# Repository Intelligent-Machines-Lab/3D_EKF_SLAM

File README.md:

# 3D EKF SLAM

<div align="center">
	<table>
	  <tr>
	    <td>Experiment</td>
	     <td>High Level reconstruction</td>
	     <td>Point cloud reconstruction</td>
	  </tr>
	  <tr>
	    <td></td>
	    <td></td>
	    <td></td>
	  </tr>
	 </table>
</div>

This repository contains the work from [Leonardo Mariga](https://github.com/leomariga) .

### [Thesis PDF](https://github.com/Intelligent-Machines-Lab/3D_EKF_SLAM/blob/main/Publications/Leonardo_Mariga_MSc_Dissertation_ITA_2021.pdf) | [Videos](https://github.com/Intelligent-Machines-Lab/3D_EKF_SLAM/tree/main/Videos) | [Presentation](https://github.com/Intelligent-Machines-Lab/3D_EKF_SLAM/blob/main/Publications/Presentation/Leonardo%20Mariga%20Master%20presentation.pdf)

> **Solving the Simultaneous Localization and 3D Mapping Problem in Mobile Robotics Using Multi-Level Parameterized Representations**<br>
> Author: **Leonardo Mariga (ITA)**
> Advisor: Prof. Dr. Cairo Lúcio Nascimento Júnior (ITA)
>
> **Simplified Abstract:** *This work proposes an expansion of the traditional landmark-based EKF-SLAM for 3D indoor environments. It uses a mobile robot with an RGBD camera to decompose a scene and update its 3dof location. A point-cloud map is reconstructed by initially simplifying the scene into cylinders and planes. Then, its points are segmented and associated to their specific EKF feature. This enables to output a map using different levels of abstraction, which is helpful when working in applications with limited memory requirements. In our feature extraction method, the RANSAC is used for planar segmentation. The non-planar points are clustered using DB-SCAN and parameterized as cylinders after passing through validation gates. On each step, the classical EKF framework propagates and updates the features' states. This also triggers the point-cloud growth and increments the point-cloud of the observed feature. Our simulation results shows that this method successfully reconstructs maps, reducing the IAE criteria to 15% of trajectory error compared to the odometry. Finally, we sucessfully validate the real environment, using a Intel RealSense camera.*

## 3D EKF SLAM: how does it work?

An overview the algorithm is illustrated in figure below as a V-shaped process. The vertical axis represents map density (which is related to its level of abstraction) and the horizontal axis is the processing order. Starting as a point cloud input and going down to a simplified primitive and parameterized local scene, the features are associated and merged to a global map.

By doing that, the robot's pose is corrected and a global high level map can be generated using the parameterized feature. If the application chooses to carry the point cloud, it can create a point cloud or voxel-based maps as output.

<div align="center">
  <br>
</div>

## Results:

### Simulation results

Simulation results shows that in spite of the odometry error slowly increasing and reaching 7 m, the estimated trajectory error is always within bounds of 1 m. As a quantification tool, we can use the  Integral Absolute Error (IAE) criteria to measure the overall error during the whole SLAM process. Table shows the IAE criteria for this case.The odometry path error is the error related to the concatenation of commands sent to the robot and the estimated path error is obtained from comparing the proposed algorithm with the real path. 

<div align="center">
	<table>
	  <tr>
	    <td></td>
	     <td>IAE Criteria</td>
	  </tr>
	  <tr>
	    <td>Odometry path error</td>
	    <td>304.28</td>
	  </tr>
	  <tr>
	    <td>Our estimation error</td>
	    <td>49.82</td>
	  </tr>
	 </table>
</div>

<div align="center">
  <br>
</div>

### Experimental results

Below are some samples of reconstructed environment with a Intel RealSense RGBD camera. 

<div align="center">
	<table>
	  <tr>
	    <td>Experiment</td>
	     <td>High Level reconstruction</td>
	     <td>Point cloud reconstruction</td>
	  </tr>
	  <tr>
	    <td></td>
	    <td></td>
	    <td></td>
	  </tr>
	  <tr>
	    <td></td>
	    <td></td>
	    <td></td>
	  </tr>
	 </table>
</div>

## Why use this method?

This algorithm uses a cylinder-and-plane combination to reconstruct a parameterized environment, and at the same time, correct the robot's pose. Different from point cloud registration techniques, the proposed algorithm does not match consecutive frames on each other. Actually, it interprets the scene and classifies each point cloud to an EKF feature. **Consequently, our solution is not only a basic SLAM technique but also a strategy for scene understanding and object segmentation.** 

Though the point cloud can be used to reconstruct a colored realistic environment, the algorithm only requires the parameterized environment to work. Therefore, it can operate in machines with different memory configurations 

### Main contributions

The main contributions of this work can be summarize as follows:

 - Use multiple abstraction layers to build a point cloud map on a landmark-based EKF-SLAM.
 - Feature growth method for different views of observed planar or arbitrary objects. 
 - Construction of a parameterized hybrid map based of simplification of the point cloud representation.

## Cite this work

```
@mastersthesis{leomariga,
author = {Mariga, Leonardo},
year = {2021},
month = {12},
pages = {123},
school = {Instituto tecnológico de aeronáutica},
title = {Solving the simultaneous localization and 3D mapping problem in mobile robotics using multi-level parameterized representations},
doi = {10.13140/RG.2.2.33836.33926}
}
```

## Contact

Author: [Leonardo Mariga](https://github.com/leomariga) 

E-mail: leomariga@gmail.com

Feel free to contact me.

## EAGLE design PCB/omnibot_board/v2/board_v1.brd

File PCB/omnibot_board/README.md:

# Omni board
The OMNI board manages power supply to the camera mount and allows communication between Arduino Nano and the camera rotation motor.

-----------------

## Schematic
<!-- 
Click [here](https://github.com/Intelligent-Machines-Lab/Omni_3D/blob/master/PCB/omnibot_board/board_v1.pdf) to open the schematic pdf.  -->

<div align="center">
  <b>
</div>

## PCB

<div align="center">
  <b>
</div>

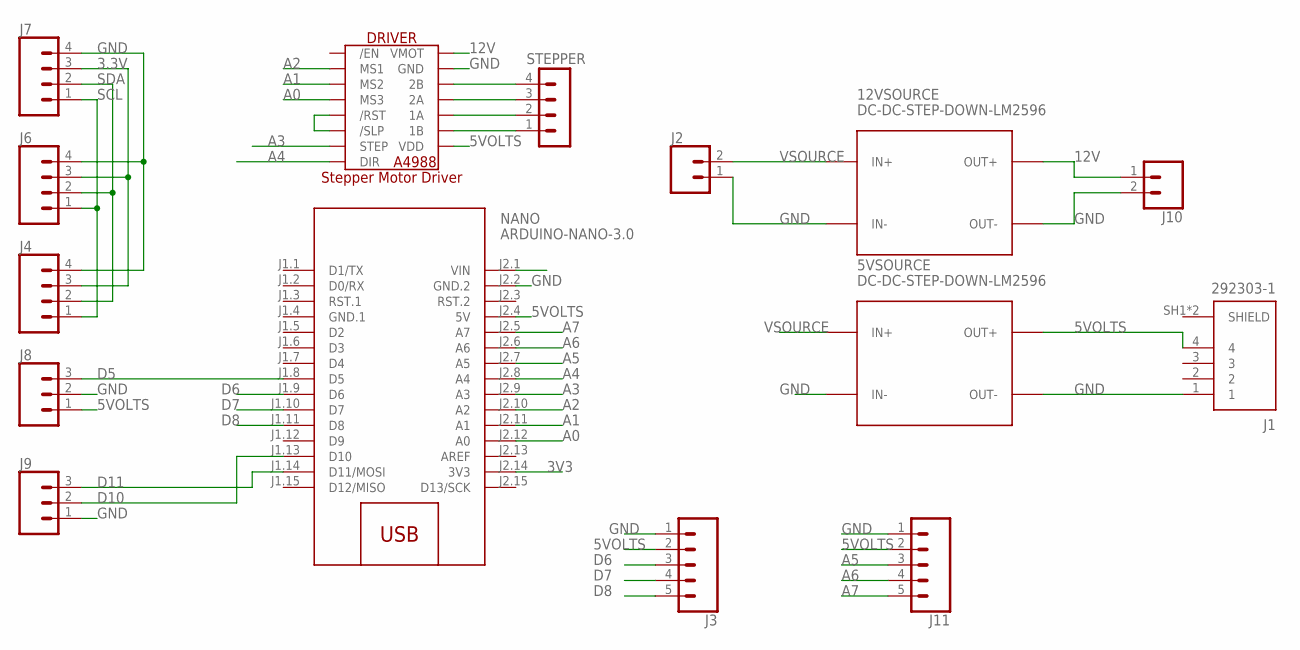
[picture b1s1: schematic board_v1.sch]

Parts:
5VSOURCE, 12VSOURCE: DC-DC-STEP-DOWN-LM2596
DRIVER: A4988_STEP
J1: 292303-1
J2, J10: CONN_025MM; SCREWTERMINAL-5MM-2
J3, J11: CONN_05; 1X05
J4, J6, J7: CONN_04POLAR; MOLEX-1X4
J8, J9: CONN_03POLAR; MOLEX-1X3
NANO: ARDUINO-NANO-3.0
STEPPER: MA04-1

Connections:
3.3V: J4.3, J6.3, J7.3
3V3: NANO.J2.14 (3V3)
5VOLTS: 5VSOURCE.OUT+, DRIVER.VDD, J1.4, J3.2, J8.1, J11.2, NANO.J2.4 (5V)
12V: 12VSOURCE.OUT+, DRIVER.VMOT, J10.1
A0: DRIVER.MS3, NANO.J2.12 (A0)
A1: DRIVER.MS2, NANO.J2.11 (A1)
A2: DRIVER.MS1, NANO.J2.10 (A2)
A3: DRIVER.STEP, NANO.J2.9 (A3)
A4: DRIVER.DIR, NANO.J2.8 (A4)
A5: J11.3, NANO.J2.7 (A5)
A6: J11.4, NANO.J2.6 (A6)
A7: J11.5, NANO.J2.5 (A7)
D5: J8.3, NANO.J1.8 (D5)
D6: J3.3, NANO.J1.9 (D6)
D7: J3.4, NANO.J1.10 (D7)
D8: J3.5, NANO.J1.11 (D8)
D10: J9.2, NANO.J1.13 (D10)
D11: J9.3, NANO.J1.14 (D11/MOSI)
GND: 5VSOURCE.IN-, 5VSOURCE.OUT-, 12VSOURCE.IN-, 12VSOURCE.OUT-, DRIVER.GND, DRIVER.GND2 (GND), J1.1, J2.1, J3.1, J4.4, J6.4, J7.4, J8.2, J9.1, J10.2, J11.1, NANO.J2.2 (GND.2)
GND.1: NANO.J1.4 (GND.1)
unnamed: DRIVER.2B, STEPPER.4
unnamed: DRIVER.2A, STEPPER.3
unnamed: DRIVER.1A, STEPPER.2
unnamed: DRIVER.1B, STEPPER.1
unnamed: DRIVER./RST, DRIVER./SLP
SCL: J4.1, J6.1, J7.1
SDA: J4.2, J6.2, J7.2
SHIELD: J1.SH1 (SHIELD), J1.SH2 (SHIELD)
VSOURCE: 5VSOURCE.IN+, 12VSOURCE.IN+, J2.2

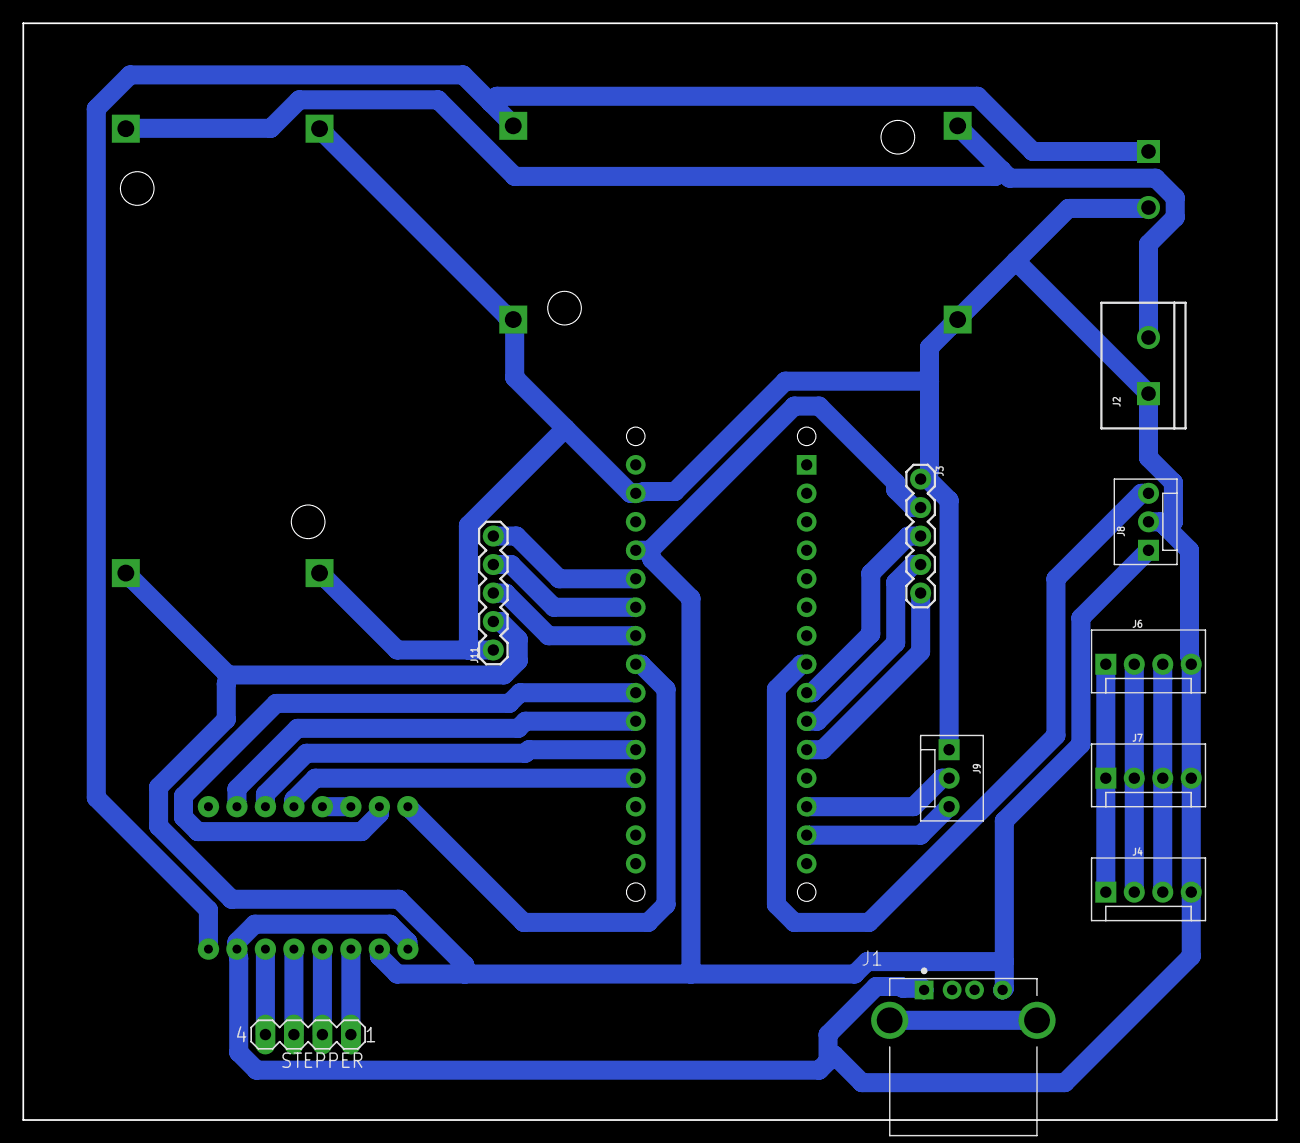
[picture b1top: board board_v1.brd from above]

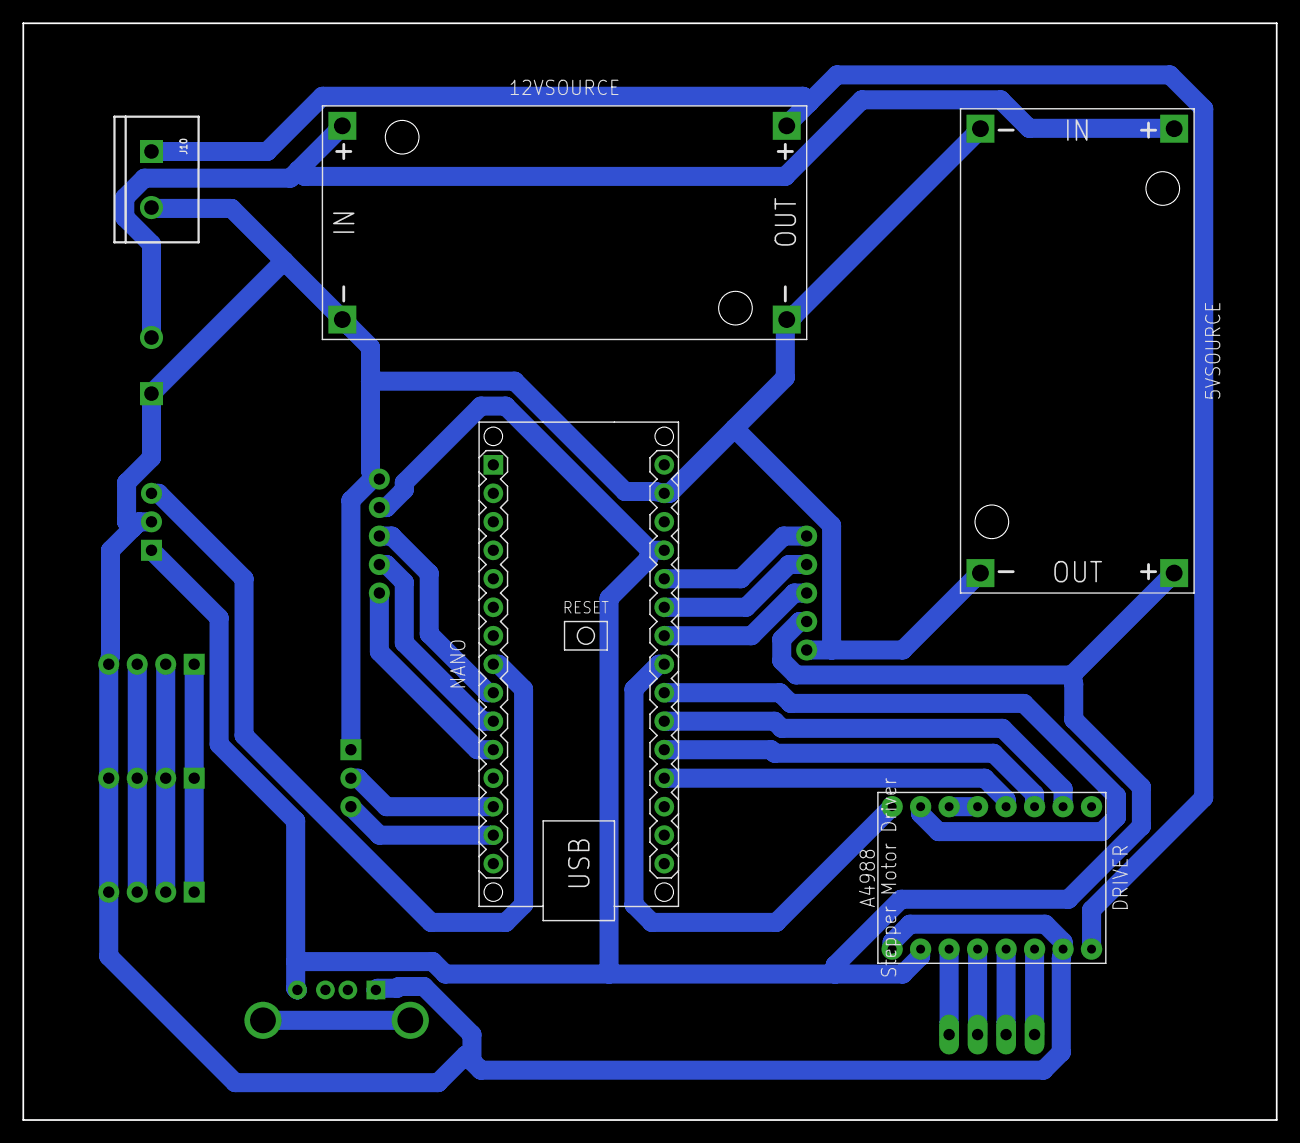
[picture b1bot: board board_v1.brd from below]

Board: 2 copper layers, 111.8 x 97.8 mm, 15 parts (5 on the bottom side), 27 nets.

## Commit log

2021-12-01 add script files
2021-12-01 add datasets and simulation codes
2022-02-20 Add video and publications
2022-02-20 Modify readme
2022-02-20 Change Readme
2022-02-20 fix Readme
2022-04-04 Add citation to Readme

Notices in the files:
parts and their libraries:
diy-modules: Released under the Creative Commons Attribution 4.0 International License: http://creativecommons.org/licenses/by/4.0
SparkFun-Connectors: Licensing: Creative Commons ShareAlike 4.0 International - https://creativecommons.org/licenses/by-sa/4.0
